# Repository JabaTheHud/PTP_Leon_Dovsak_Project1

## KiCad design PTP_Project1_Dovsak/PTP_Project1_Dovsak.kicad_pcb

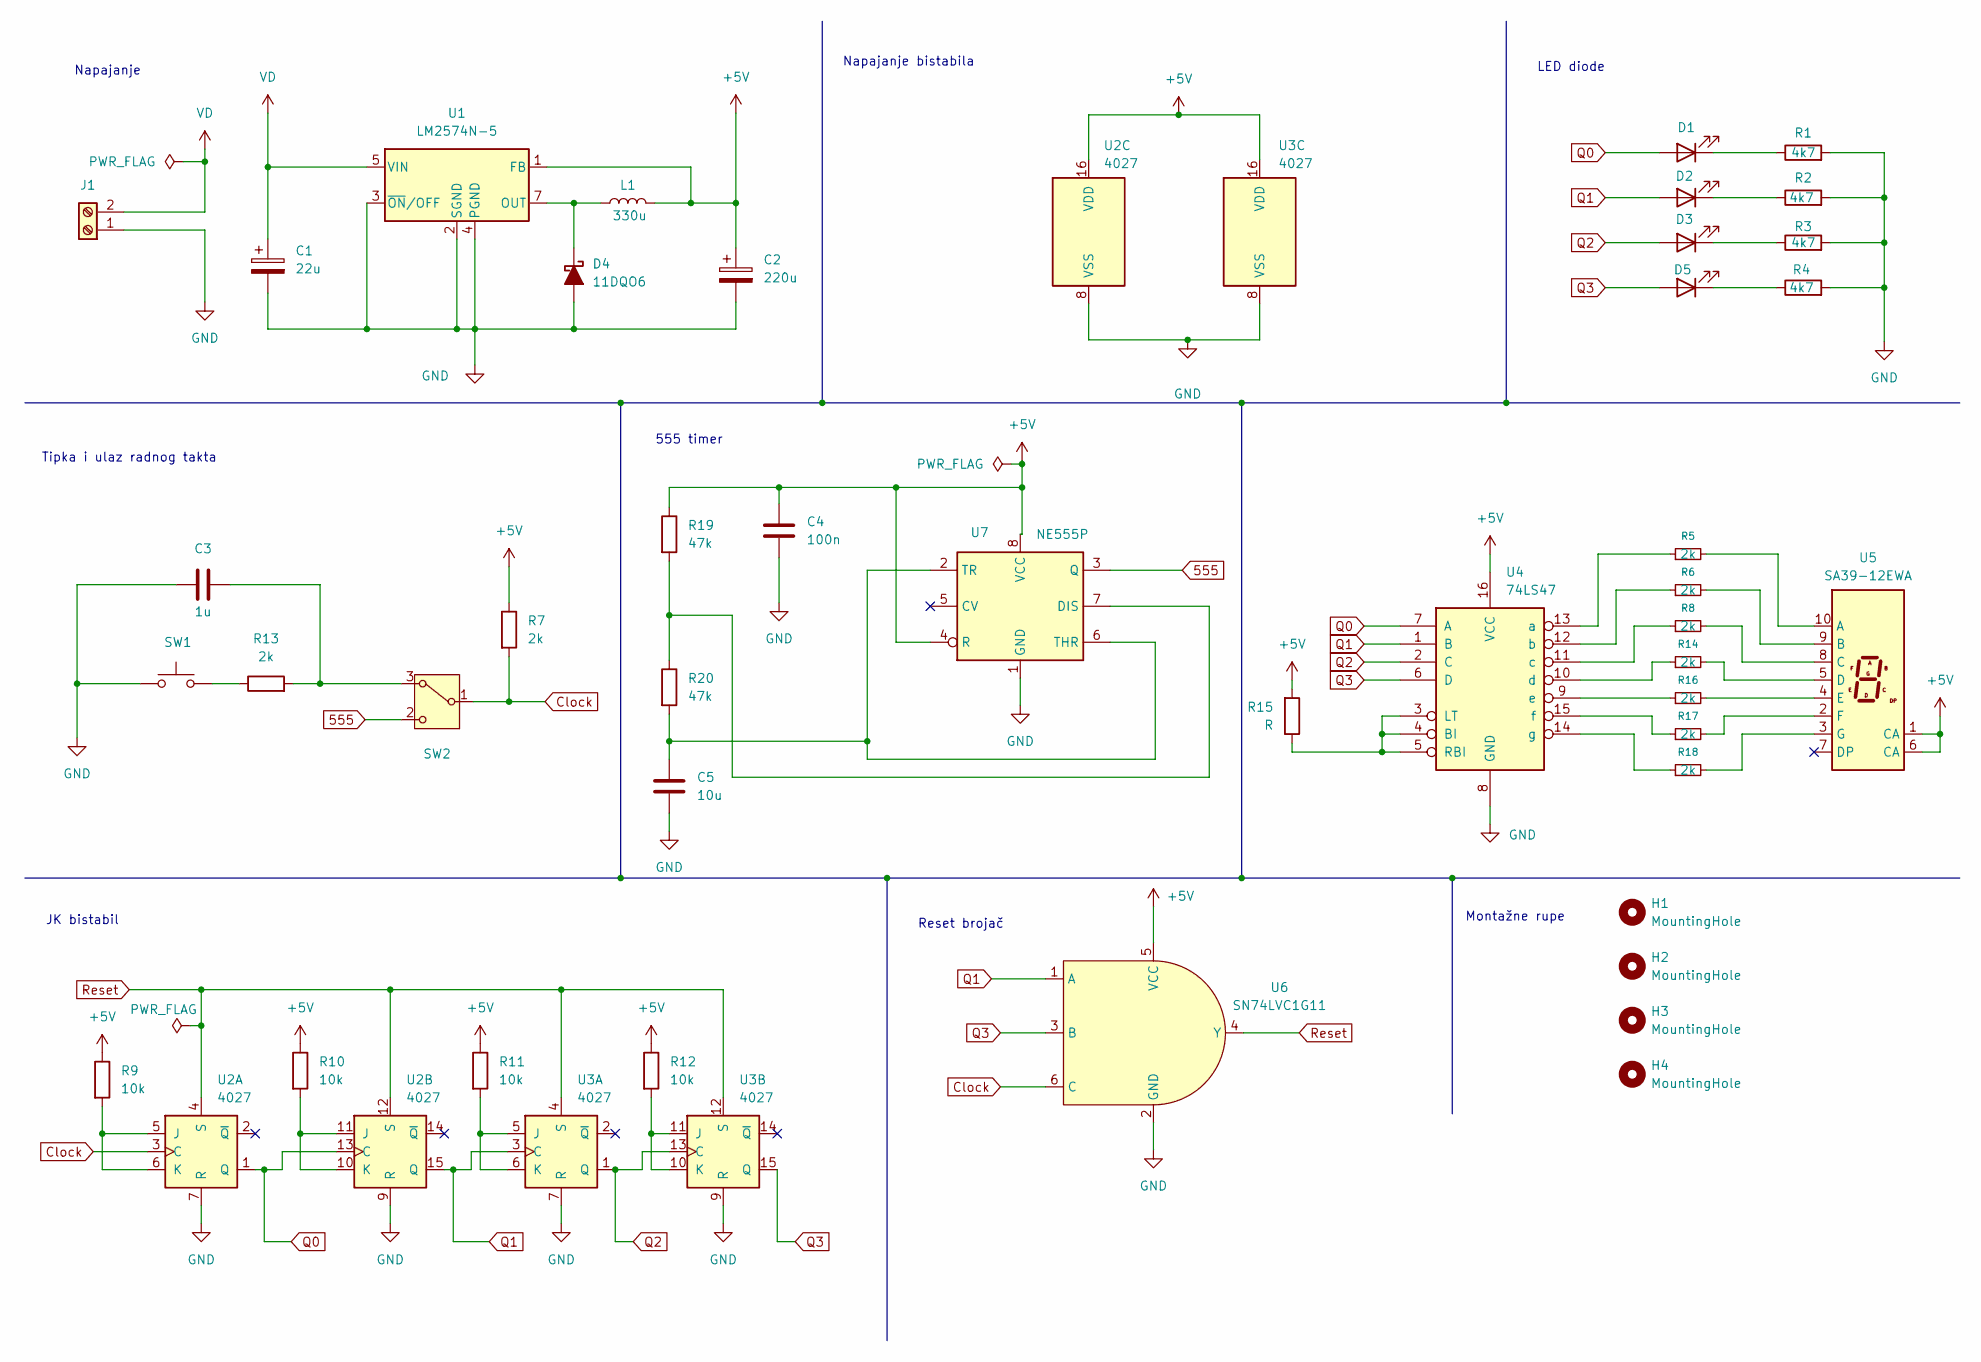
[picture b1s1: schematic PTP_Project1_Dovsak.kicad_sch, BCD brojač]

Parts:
C1: 22u; CP_Radial_D5.0mm_P2.00mm
C2: 220u; CP_Radial_D5.0mm_P2.00mm
C3: 1u; C_1206_3216Metric_Pad1.33x1.80mm_HandSolder
C4: 100n; C_1206_3216Metric_Pad1.33x1.80mm_HandSolder
C5: 10u; C_1206_3216Metric_Pad1.33x1.80mm_HandSolder
D1, D2, D3, D5: LED_D5.0mm
D4: 11DQO6; D_DO-41_SOD81_P12.70mm_Horizontal
H1, H2, H3, H4: MountingHole; MountingHole_5.5mm
J1: TerminalBlock_MetzConnect_Type011_RT05502HBLC_1x02_P5.00mm_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
L1: 330u; L_Radial_D7.2mm_P3.00mm_Murata_1700
R1, R2, R3, R4: 4k7; R_Axial_DIN0207_L6.3mm_D2.5mm_P10.16mm_Horizontal
R5, R6, R7, R8, R13, R14, R16, R17, R18: 2k; R_1206_3216Metric_Pad1.30x1.75mm_HandSolder
R9, R10, R11, R12: 10k; R_1206_3216Metric_Pad1.30x1.75mm_HandSolder
R15: R; R_1206_3216Metric_Pad1.30x1.75mm_HandSolder
R19, R20: 47k; R_1206_3216Metric_Pad1.30x1.75mm_HandSolder
SW1: SW_PUSH_6mm_H4.3mm
SW2: SW_Slide_SPDT_Straight_CK_OS102011MS2Q
U1: LM2574N-5; DIP-8_W7.62mm_Socket_LongPads; Manufacturer Part Number LM2574N-5G
U2, U3: 4027; DIP-16_W7.62mm_Socket_LongPads; Manufacturer Part Number CD4027BMS
U4: 74LS47; DIP-16_W7.62mm_Socket_LongPads
U5: SA39-12EWA; HDSP-7401
U6: SN74LVC1G11; SOT-23-6
U7: NE555P; DIP-8_W7.62mm

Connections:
555: SW2.2 (A), U7.3 (Q)
+5V: C2.1, C4.1, L1.2, R7.1, R9.1, R10.1, R11.1, R12.1, R15.2, R19.1, U1.1 (FB), U2.16 (VDD), U3.16 (VDD), U4.16 (VCC), U5.1 (CA), U5.6 (CA), U6.5 (VCC), U7.4 (R), U7.8 (VCC)
Clock: R7.2, SW2.1 (B), U2.3 (C), U6.6 (C)
GND: C1.2, C2.2, C3.1, C4.2, C5.2, D4.2 (A), J1.1, R1.2, R2.2, R3.2, R4.2, SW1.1, U1.2 (SGND), U1.3 (~ON/OFF), U1.4 (PGND), U2.7 (R), U2.8 (VSS), U2.9 (R), U3.7 (R), U3.8 (VSS), U3.9 (R), U4.8 (GND), U6.2 (GND), U7.1 (GND)
unnamed: D1.1 (K), R1.1
unnamed: D2.1 (K), R2.1
unnamed: D3.1 (K), R3.1
unnamed: D4.1 (K), L1.1, U1.7 (OUT)
unnamed: D5.1 (K), R4.1
unnamed: R13.1, SW1.2
unnamed: C3.2, R13.2, SW2.3 (C)
unnamed: R9.2, U2.5 (J), U2.6 (K)
unnamed: R10.2, U2.10 (K), U2.11 (J)
unnamed: R11.2, U3.5 (J), U3.6 (K)
unnamed: R12.2, U3.10 (K), U3.11 (J)
unnamed: R15.1, U4.3 (LT), U4.4 (BI), U4.5 (RBI)
unnamed: R5.1, U4.13 (a)
unnamed: R6.1, U4.12 (b)
unnamed: R8.1, U4.11 (c)
unnamed: R14.1, U4.10 (d)
unnamed: R16.1, U4.9 (e)
unnamed: R17.1, U4.15 (f)
unnamed: R18.1, U4.14 (g)
unnamed: R5.2, U5.10 (A)
unnamed: R6.2, U5.9 (B)
unnamed: R8.2, U5.8 (C)
unnamed: R14.2, U5.5 (D)
unnamed: R16.2, U5.4 (E)
unnamed: R17.2, U5.2 (F)
unnamed: R18.2, U5.3 (G)
unnamed: R19.2, R20.1, U7.7 (DIS)
unnamed: C5.1, R20.2, U7.2 (TR), U7.6 (THR)
Q0: D1.2 (A), U2.1 (Q), U2.13 (C), U4.7 (A)
Q1: D2.2 (A), U2.15 (Q), U3.3 (C), U4.1 (B), U6.1 (A)
Q2: D3.2 (A), U3.1 (Q), U3.13 (C), U4.2 (C)
Q3: D5.2 (A), U3.15 (Q), U4.6 (D), U6.3 (B)
Reset: U2.4 (S), U2.12 (S), U3.4 (S), U3.12 (S), U6.4 (Y)
VD: C1.1, J1.2, U1.5 (VIN)

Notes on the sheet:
Napajanje bistabila
Montažne rupe
Napajanje
JK bistabil
LED diode
Tipka i ulaz radnog takta
Reset brojač
555 timer

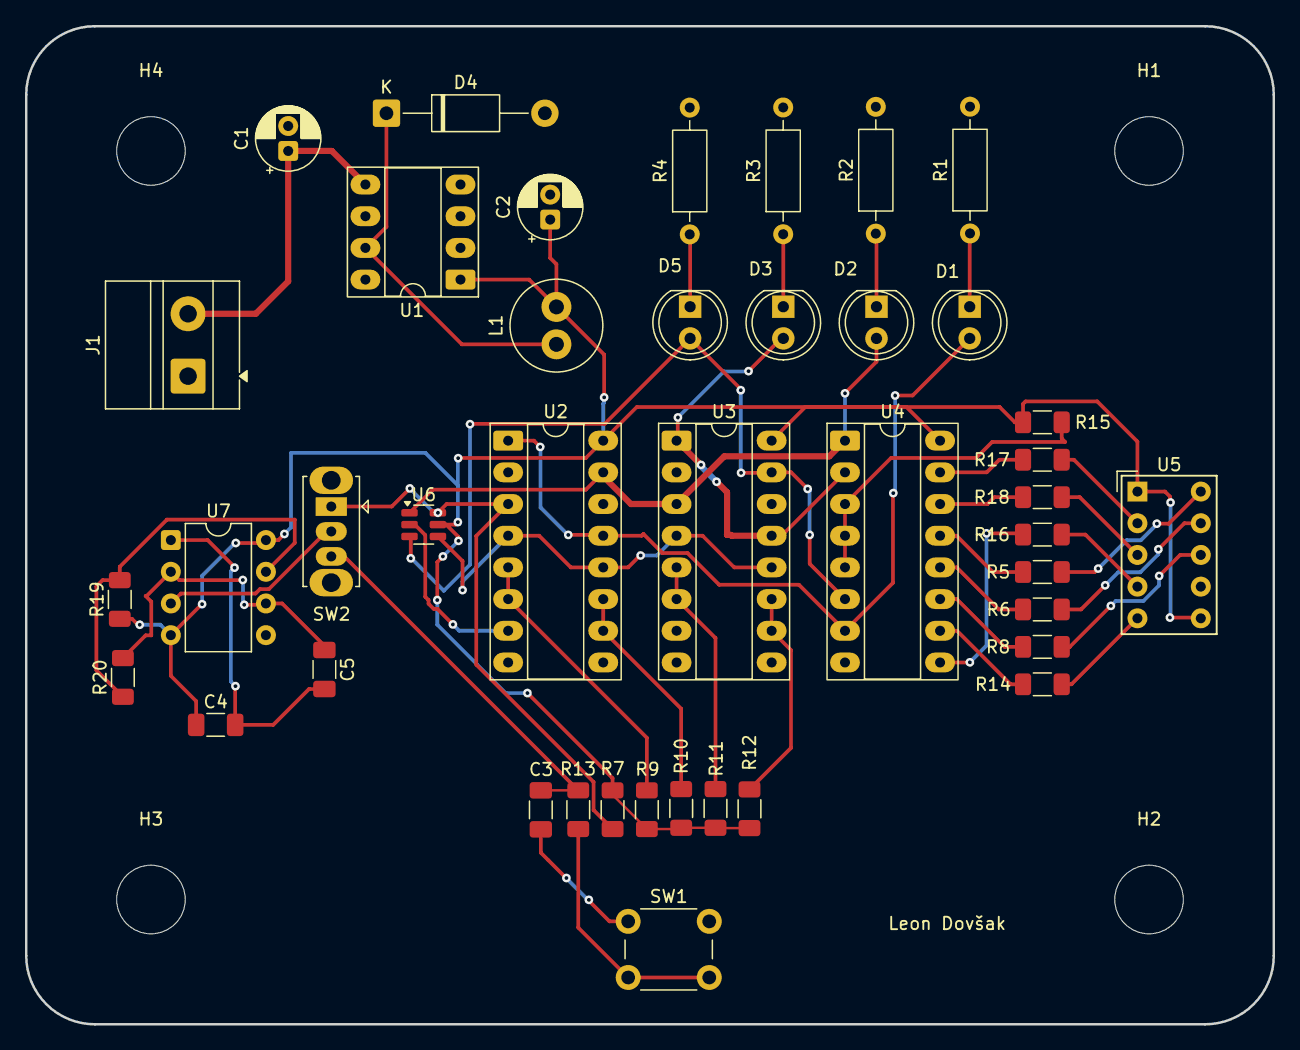
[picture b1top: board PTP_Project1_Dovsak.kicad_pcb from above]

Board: 2 copper layers, 100.0 x 80.0 mm, 45 parts (0 on the bottom side), 38 nets.

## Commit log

2025-10-21 ispunjena sastavnica
2025-10-28 LV2 rijesen
2025-11-04 LV3
    Zavrsena VL3
2025-11-11 LV4 rijesen
    zavrsena lv4
2025-11-25 LV 5 rijesen
2025-12-09 LV8_gotova
    LV 8 je gotova
2025-12-16 Gotova LV potpuno
